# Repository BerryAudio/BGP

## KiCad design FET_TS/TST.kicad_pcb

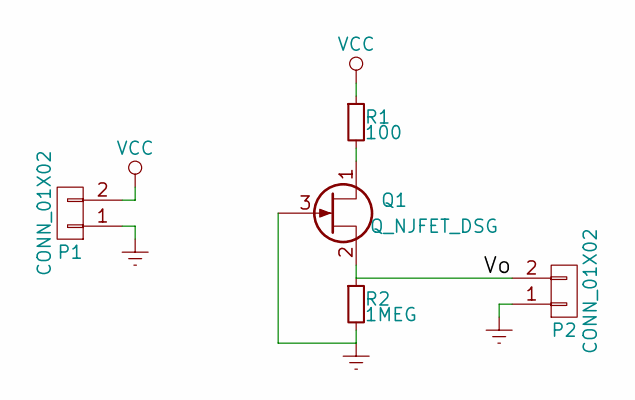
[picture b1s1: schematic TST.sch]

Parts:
P1, P2: CONN_01X02; Pin_Header_Straight_1x02
Q1: Q_NJFET_DSG; SOT-23_Handsoldering
R1: 100; R_0603_HandSoldering
R2: 1MEG; R_0603_HandSoldering

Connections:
/Vo: P2.2, Q1.2 (S), R2.1
Earth: P1.1, P2.1, Q1.3 (G), R2.2
unnamed: Q1.1 (D), R1.2
VCC: P1.2, R1.1

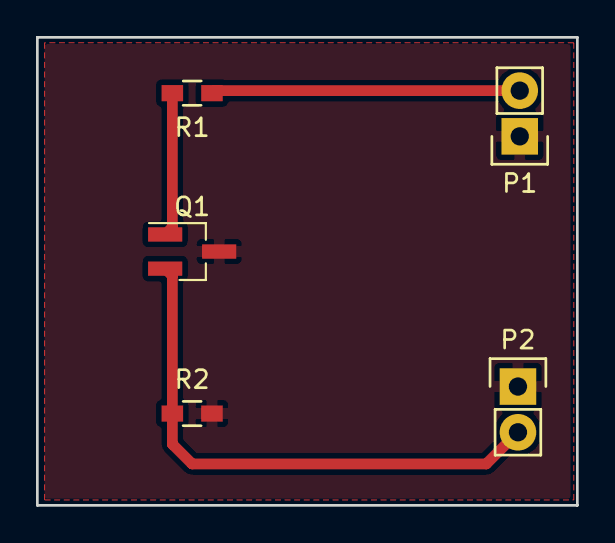
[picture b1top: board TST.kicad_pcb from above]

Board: 2 copper layers, 30.0 x 26.0 mm, 5 parts (0 on the bottom side), 4 nets.
